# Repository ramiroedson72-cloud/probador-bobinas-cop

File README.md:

# Probador de bobinas COP — ESP32-C3 Super Mini

Generador de disparos PWM para probar bobinas de encendido (COP). Un potenciómetro
controla la frecuencia (10–200 Hz ≈ 300–6000 RPM en motor de 4 cilindros) y el
firmware mantiene un **dwell fijo de 3 ms** recalculando el duty. La pantalla
**OLED 128×64 I2C** muestra RPM, frecuencia, dwell y el logo SISU.

Diseñado por **Ramiro** · Logo SISU en la serigrafía inferior de la placa.

## Carcasa imprimible

Los archivos `carcasa.gcode` y `tapa carcasa.gcode` están listos para impresión
y fueron generados con OrcaSlicer.

## Estructura del repositorio

| Carpeta / archivo | Contenido |
|---|---|
| `Probador_Bobinas.ino` | Firmware para ESP32-C3 (Arduino) |
| `Probador_Bobinas_PCB/` | Proyecto KiCad 10 (esquemático + placa) |
| `Probador_Bobinas_PCB/PARA_FABRICAR/` | **Gerbers ZIP** — se sube tal cual a JLCPCB/PCBWay (2 capas, 1.6 mm, 1 oz) |
| `Probador_Bobinas_PCB/fabricacion/` | STEP 3D de la placa armada, esquemático PDF y BOM CSV |
| `PCB bobina Imprimir/` | PDFs 1:1 para **fabricación casera**: cobre para planchar (2), máscara UV (2), serigrafía (2) y STEP del LCD 20x4 para la carcasa |
| `Carcasa del probador de bobinas/` | G-code de la carcasa y la tapa, más su render conjunto |
| `libreria_kicad_SnapEDA/` | Librería KiCad autocontenida: símbolos, footprints y modelos 3D de todas las partes no estándar |

> Para abrir el proyecto KiCad en otra PC: registrar `libreria_kicad_SnapEDA` como
> librería "SnapEDA" (símbolos y footprints) en las tablas globales.

## La placa

- 61 × 74 × 1.6 mm, doble cara, componentes THT (pensada para soldar a mano)
- Etapa de potencia: **IGBT FGH60N60SFD** (600 V / 60 A, TO-247) con zener 15 V
  gate-emisor — reemplaza al IRLZ44N del prototipo (que avalanchaba a 55 V)
- Alimentación lógica: módulo **LM2596** 12 V → 5 V
- Clemas WAGO 236-402 (12 V y bobina), potenciómetro WH148 al borde (panel),
  header 1x4 para la pantalla OLED I2C
- Reglas de diseño: pista del colector con **2.5 mm de separación** (flyback
  ~400 V), potencia a 2 mm (10 A pulsados), señales a 0.8 mm (aptas para planchado)
- Plano de tierra cuadriculado en ambas caras; taladros M3 de esquina **H1/H2/H4
  con anillo a GND** para aterrizar la carcasa metálica (H3 solo mecánico)
- Rutas de refuerzo con alambre marcadas en la capa `Cmts.User` (retorno GND,
  colector 300 V y VCC de bobina) para la versión casera

## Cableado externo

| Conexión | Detalle |
|---|---|
| Clema J2 | Entrada 12 V (batería/fuente que aguante picos de 5–10 A) + fusible 5 A externo |
| Clema J1 | Primario de la bobina COP |
| Header J3 | OLED 128×64 I2C: 5V · GND · SDA (GPIO8) · SCL (GPIO9) |
| Cuerpo (rosca) de la bujía | GND de potencia — sin esto no hay chispa |

## Compilar y subir (Arduino IDE)

1. Instalar el core ESP32: Preferencias → URLs adicionales →
   `https://espressif.github.io/arduino-esp32/package_esp32_index.json`,
   luego Boards Manager → instalar "esp32 by Espressif Systems".
2. Instalar las librerías **Adafruit GFX** y **Adafruit SSD1306**.
3. Placa: **ESP32C3 Dev Module**, con **USB CDC On Boot: Enabled**.
4. Compilar y subir. Si no entra en modo de programación: mantener BOOT,
   pulsar RESET, soltar BOOT.

El sketch es compatible con el core ESP32 v2.x y v3.x (detecta la API de LEDC
automáticamente).

## Fabricación

**Profesional:** subir `PARA_FABRICAR/Probador_Bobinas_GERBERS.zip` a JLCPCB —
2 capas, 1.6 mm, cobre 1 oz, resto por defecto. (El PCBA no aplica: el ESP32
SuperMini y el módulo LM2596 son módulos de aftermarket que se sueldan a mano.)

**Casera (planchado + máscara UV):** PDFs en `PCB bobina Imprimir/`, impresora
láser a escala 100 % (el contorno debe medir 61 × 74 mm). Los archivos indican
en su nombre si van espejados o no. Las 7 vías se hacen con alambre pasante
soldado por ambos lados. Máscara UV: imprimir 2 acetatos por cara y encimarlos.

## Advertencias

- El primario genera picos de 300–400 V al cortar. El IGBT los soporta con
  margen, pero usar **disipador** en sesiones largas (hay espacio junto a Q1).
- No poner diodo flyback ni TVS en el primario: mata la chispa.
- Mantener los cables de alta tensión lejos del ESP32 (el EMI de la chispa
  puede resetearlo).
- Probar siempre con bujía o chispómetro conectado a la bobina.

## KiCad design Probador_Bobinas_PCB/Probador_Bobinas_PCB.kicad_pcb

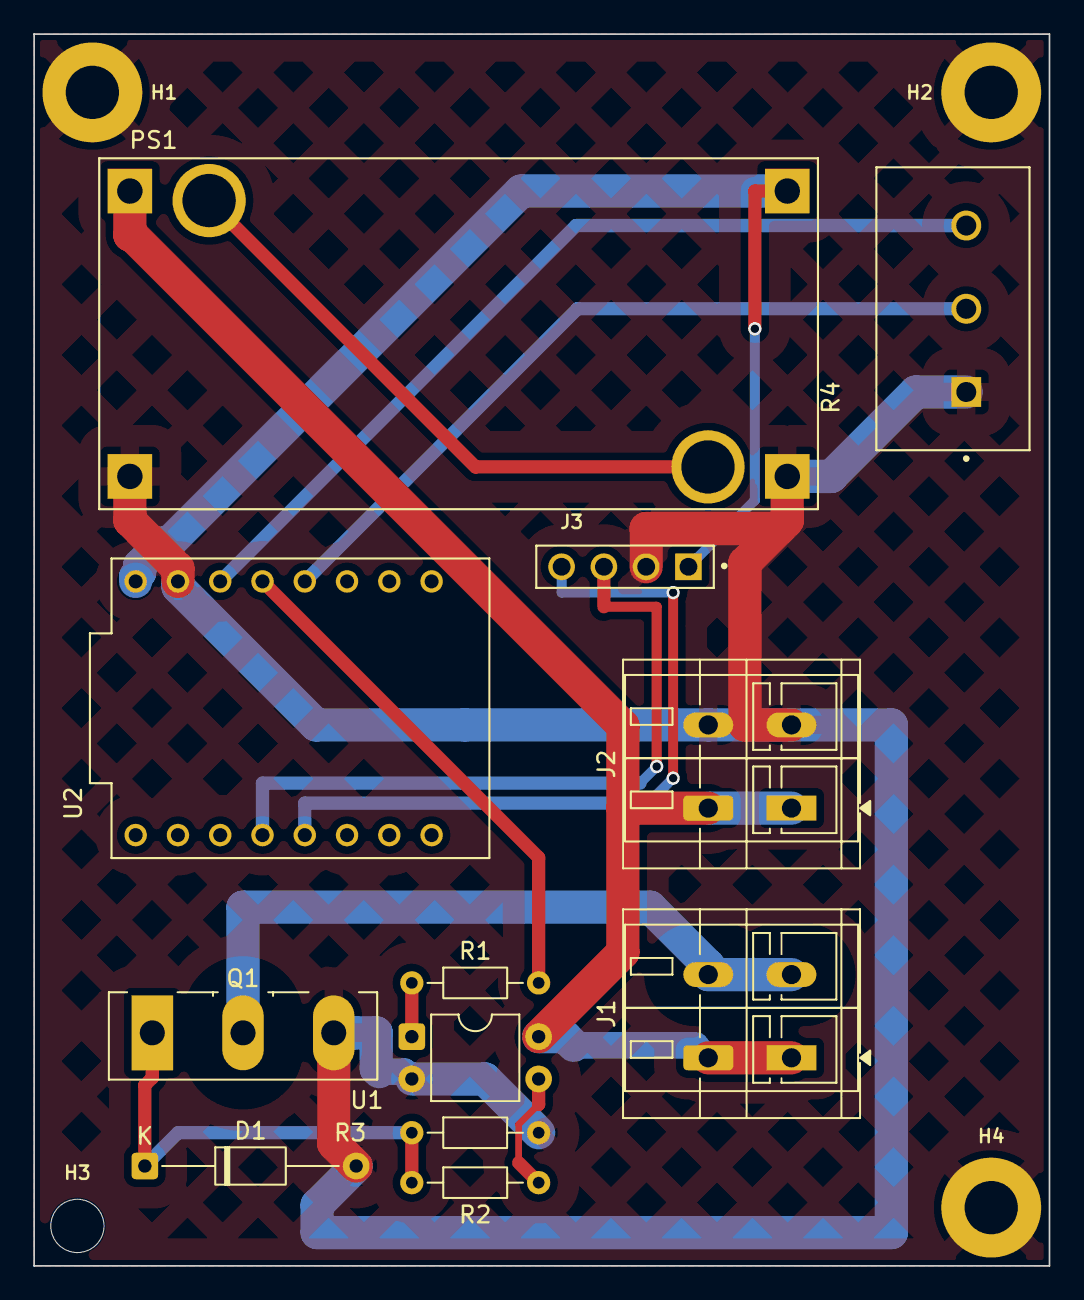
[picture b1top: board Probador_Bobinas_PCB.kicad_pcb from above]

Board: 2 copper layers, 61.0 x 74.0 mm, 16 parts (0 on the bottom side), 13 nets.

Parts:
D1: D_Zener 15V; D_DO-35_SOD27_P12.70mm_Horizontal
H1, H2, H3, H4: M3; MountingHole_M3
J1, J2: WAGO_236-402; TerminalBlock_WAGO_236-402_1x02_P5.00mm_45Degree
J3: PPTC041LFBN-RC; SULLINS_PPTC041LFBN-RC
PS1: MC00100; CONV_MC00100
Q1: FGH60N60SFD; TO-247-3_Vertical
R1: R_150; R_Axial_DIN0204_L3.6mm_D1.6mm_P7.62mm_Horizontal
R2: R_100; R_Axial_DIN0204_L3.6mm_D1.6mm_P7.62mm_Horizontal
R3: R_560; R_Axial_DIN0204_L3.6mm_D1.6mm_P7.62mm_Horizontal
R4: WH148-1A-2-18T-L20; TRIM_WH148-1A-2-18T-L20
U1: PC817; DIP-4_W7.62mm
U2: ESP32-C3_SUPERMINI_TH; MODULE_ESP32-C3_SUPERMINI_TH

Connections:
Earth: D1.2 (A), H1.1, H2.1, H4.1, J2.2, J3.2, PS1.IN-, PS1.OUT-, Q1.3 (E), R3.2, R4.1, U1.2, U2.G (GND)
unnamed: D1.1 (K), Q1.1 (G), R2.1, R3.1
unnamed: J1.2, Q1.2 (C)
unnamed: J3.1, PS1.OUT+, U2.5V
unnamed: PS1.MH1 (MOUTING), PS1.MH2 (MOUTING)
unnamed: R1.1, U1.1
unnamed: R2.2, U1.3
unnamed: R4.3, U2.3.3 (3V3)
unnamed: R4.2, U2.3 (GPIO3)
unnamed: R1.2, U2.4 (GPIO4)
unnamed: J3.3, U2.8 (GPIO8)
unnamed: J3.4, U2.9 (GPIO9)
VCC: J1.1, J2.1, PS1.IN+, U1.4
